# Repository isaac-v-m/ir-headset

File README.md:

# IR Headset

Prototype IR headset built around the Lantronix Open-Q 624A (APQ8053) development
kit. Custom hardware is limited to 2-layer boards.

## Boards

| Board | Status |
|---|---|
| `IR_Headset.kicad_sch` / `.kicad_pcb`: LTE interface board | Schematic done (ERC clean); PCB has all parts, not yet routed |

The LTE interface board connects a NimbeLink Skywire NL-SW-LTE-S7648 modem to the
dev kit's J1 GPIO header over a 40-way ribbon (2.54 mm assumed; verify on your carrier):

- 4-wire UART on BLSP1 (GPIO0 TX, GPIO1 RX, GPIO2 CTS_N, GPIO3 RFR_N), 1.8 V logic via Skywire VREF
- Modem power from the kit's 5 V rail through a 1.1 A polyfuse with 470 uF bulk capacitance
- Open-collector NPN drivers: GPIO96 -> PWR_ON, GPIO98 -> RESET_nIN (GPIO high = asserted)

## Other parts (no custom board)

| Part | Connection |
|---|---|
| Open-Q 624A SOM | Dev kit carrier (its 0.4 mm DF40 connectors need a 6+ layer fab) |
| LITE-ON WCBN3510A Wi-Fi/BT | Built into the SOM; 3 MHF4 antenna ports |
| Taoglas AP.17E GPS | SOM GNSS U.FL, which supplies +2.7 V antenna bias |
| Skywire LTE antennas | Module U.FL: X1 primary, X2 diversity |
| Near-eye display | Prototype: dev kit HDMI -> Sony ECX335 HDMI driver board. Final: 0.49" FHD MIPI DSI micro-OLED on dev kit J2 |
| Camera | 16 mm M12 lens (use the no-IR-cut / 850 nm pass version) on a sensor board on dev kit J4/J5 |

## References

- [NimbeLink NL-SW-LTE-S7648 datasheet](https://www.bipom.com/documents/skywire/1001720_NL-SW-LTE-S7648_Datasheet.pdf)
- [Open-Q 624A SOM datasheet](https://cdn.lantronix.com/wp-content/uploads/pdf/PDS-0011-OpenQ624A_SOM_HW-Datasheet.pdf)
- [Open-Q 624A Development Kit User Guide](https://cdn.lantronix.com/wp-content/uploads/pdf/Open-Q-624A-Development-Kit-User-Guide.pdf)
- [Taoglas AP.17E datasheet](https://www.taoglas.com/datasheets/AP.17E.07.0064A.pdf)

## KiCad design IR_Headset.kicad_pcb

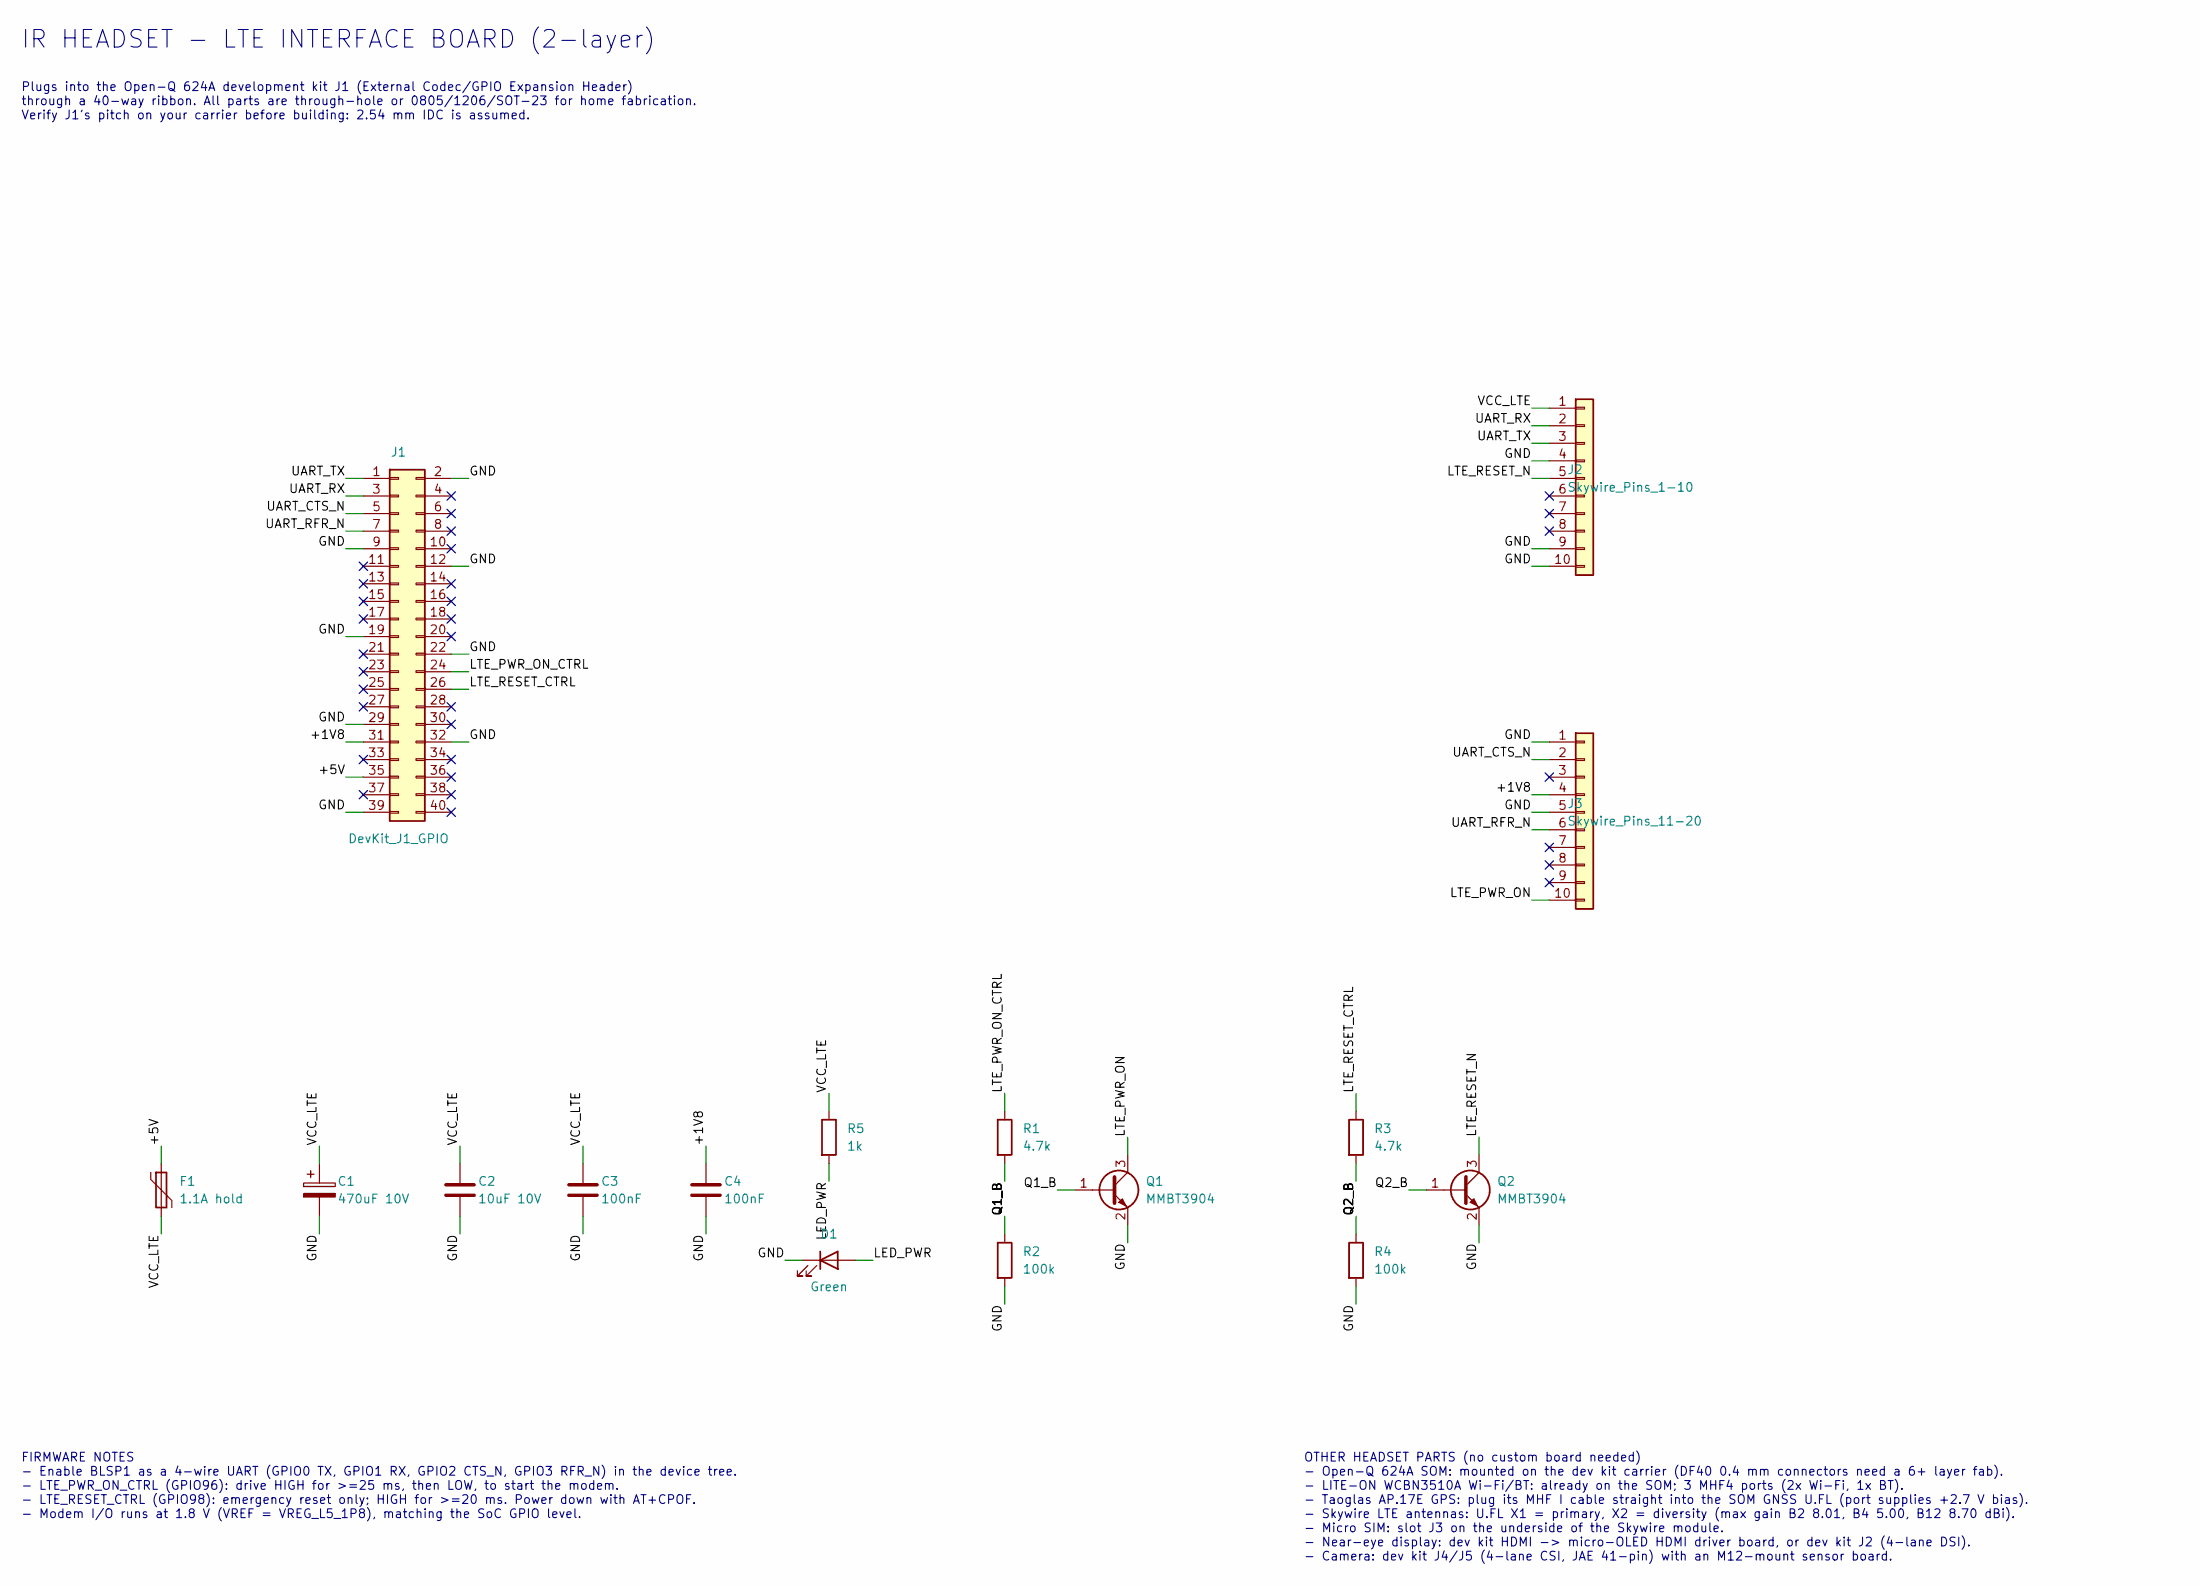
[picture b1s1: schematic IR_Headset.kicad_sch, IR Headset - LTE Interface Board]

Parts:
C1: 470uF 10V; CP_Radial_D10.0mm_P5.00mm
C2: 10uF 10V; C_0805_2012Metric
C3, C4: 100nF; C_0805_2012Metric
D1: Green; LED_D3.0mm
F1: 1.1A hold; Fuse_1206_3216Metric
J1: DevKit_J1_GPIO; IDC-Header_2x20_P2.54mm_Vertical
J2: Skywire_Pins_1-10; PinSocket_1x10_P2.00mm_Vertical
J3: Skywire_Pins_11-20; PinSocket_1x10_P2.00mm_Vertical
Q1, Q2: MMBT3904; SOT-23
R1, R3: 4.7k; R_0805_2012Metric
R2, R4: 100k; R_0805_2012Metric
R5: 1k; R_0805_2012Metric

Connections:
/+1V8: C4.1, J1.31, J3.4
/+5V: F1.1, J1.35
/GND: C1.2, C2.2, C3.2, C4.2, D1.1 (K), J1.2, J1.9, J1.12, J1.19, J1.22, J1.29, J1.32, J1.39, J2.4, J2.9, J2.10, J3.1, J3.5, Q1.2 (E), Q2.2 (E), R2.2, R4.2
/LED_PWR: D1.2 (A), R5.2
/LTE_PWR_ON: J3.10, Q1.3 (C)
/LTE_PWR_ON_CTRL: J1.24, R1.1
/LTE_RESET_CTRL: J1.26, R3.1
/LTE_RESET_N: J2.5, Q2.3 (C)
/Q1_B: Q1.1 (B), R1.2, R2.1
/Q2_B: Q2.1 (B), R3.2, R4.1
/UART_CTS_N: J1.5, J3.2
/UART_RFR_N: J1.7, J3.6
/UART_RX: J1.3, J2.2
/UART_TX: J1.1, J2.3
/VCC_LTE: C1.1, C2.1, C3.1, F1.2, J2.1, R5.1

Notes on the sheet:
IR HEADSET - LTE INTERFACE BOARD (2-layer)
Plugs into the Open-Q 624A development kit J1 (External Codec/GPIO Expansion Header) through a 40-way ribbon. All parts are through-hole or 0805/1206/SOT-23 for home fabrication. Verify J1's pitch on your carrier before building: 2.54 mm IDC is assumed.
FIRMWARE NOTES - Enable BLSP1 as a 4-wire UART (GPIO0 TX, GPIO1 RX, GPIO2 CTS_N, GPIO3 RFR_N) in the device tree. - LTE_PWR_ON_CTRL (GPIO96): drive HIGH for >=25 ms, then LOW, to start the modem. - LTE_RESET_CTRL (GPIO98): emergency reset only; HIGH for >=20 ms. Power down with AT+CPOF. - Modem I/O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
OTHER HEADSET PARTS (no custom board needed) - Open-Q 624A SOM: mounted on the dev kit carrier (DF40 0.4 mm connectors need a 6+ layer fab). - LITE-ON WCBN3510A Wi-Fi/BT: already on the SOM; 3 MHF4 ports (2x Wi-Fi, 1x BT). - Taoglas AP.17E GPS: plug its MHF I cable straight into the SOM GNSS U.FL (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

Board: 2 copper layers, 16 parts (0 on the bottom side), 15 nets, no tracks yet.
